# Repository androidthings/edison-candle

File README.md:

Edison Candle
=============
The Edison Candle is an example of building a production device using a
System-on-Module (SoM) running Android Things.
This repository contains the application software.
You can find the hardware schematic, layout, and bill of materials (BOM) hosted
on [CircuitHub](https://circuithub.com/projects/androidthings/edison-candle).

Prerequisites
-------------

- Carrier board from
  [CircuitHub](https://circuithub.com/projects/androidthings/edison-candle)
- Edison compute module ([SparkFun](https://www.sparkfun.com/products/13024))
- Edison mounting hardware ([SparkFun](https://www.sparkfun.com/products/13187))
- Orange LED ([SparkFun](https://www.sparkfun.com/products/12645))
- Yellow LED ([SparkFun](https://www.sparkfun.com/products/10634))
- Android Studio 2.2+

Getting Started
----------------

1.  Assemble the hardware components
2.  Import the project into Android Studio
3.  Connect the Edison to USB
4.  In Android Studio, click on the "Run" button.

If you prefer to run on the command line, type
```bash
./gradlew installDebug
adb shell am start com.example.androidthings.candle/.HomeActivity
```

Prototype Schematic
--------------------

You may also choose to run the sample on an Edison developer kit, with the
necessary peripherals connected as shown below:

Enable auto-launch behavior
---------------------------

This sample app is currently configured to launch only when deployed from your
development machine. To enable the main activity to launch automatically on boot,
add the following `intent-filter` to the app's manifest file:

```xml
<activity ...>

    <intent-filter>
        <action android:name="android.intent.action.MAIN"/>
        <category android:name="android.intent.category.HOME"/>
        <category android:name="android.intent.category.DEFAULT"/>
    </intent-filter>

</activity>
```

License
-------

Copyright 2017 The Android Open Source Project, Inc.

Licensed to the Apache Software Foundation (ASF) under one or more contributor
license agreements.  See the NOTICE file distributed with this work for
additional information regarding copyright ownership.  The ASF licenses this
file to you under the Apache License, Version 2.0 (the "License"); you may not
use this file except in compliance with the License.  You may obtain a copy of
the License at

  http://www.apache.org/licenses/LICENSE-2.0

Unless required by applicable law or agreed to in writing, software
distributed under the License is distributed on an "AS IS" BASIS, WITHOUT
WARRANTIES OR CONDITIONS OF ANY KIND, either express or implied.  See the
License for the specific language governing permissions and limitations under
the License.

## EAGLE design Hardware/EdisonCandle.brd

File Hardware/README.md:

Edison Candle Hardware
======================

This directory contains the hardware design files for the Edison Candle
production carrier board. The current revision was built using EAGLE.

Libraries
---------

The following EAGLE libraries were used in this design:

-   [SparkFun Blocks Template](https://github.com/sparkfun/Sparkfun_Blocks_Template)
    -   Provides Edison compute module and PCB footprint.
-   [SparkFun Eagle Libraries](https://github.com/sparkfun/SparkFun-Eagle-Libraries)
    -   Provides common components, such as the USB Micro connector.

License
-------

The hardware design files are released under the
[Creative Commons 4.0 International](http://creativecommons.org/licenses/by/4.0/)
license.

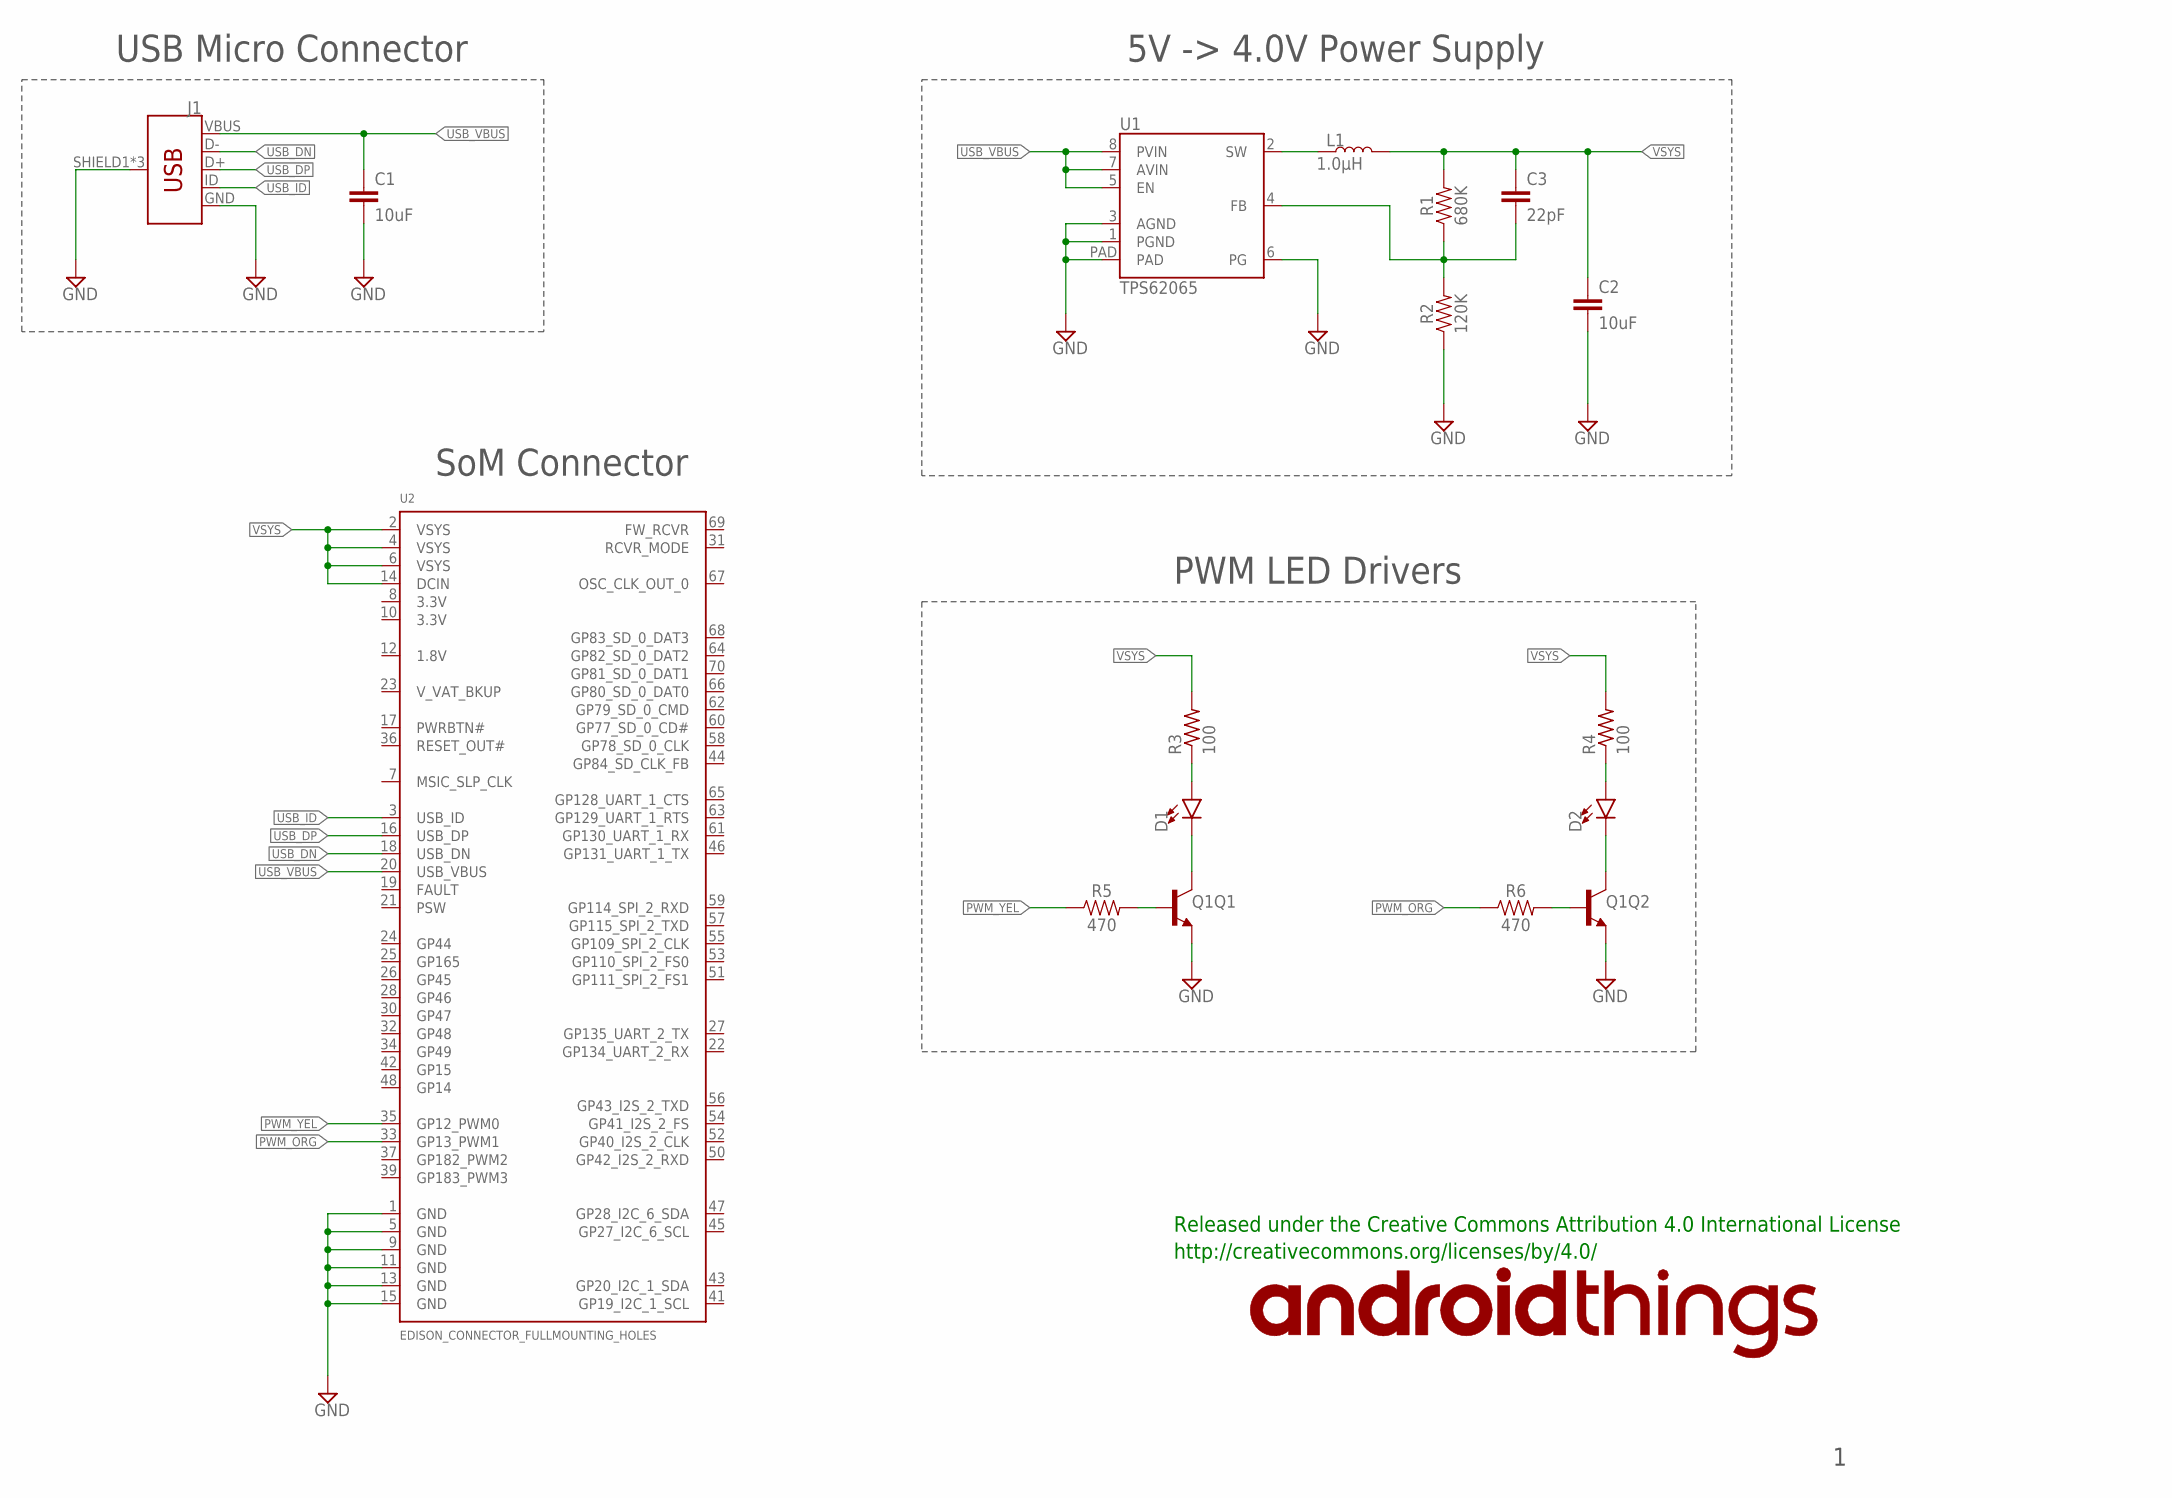
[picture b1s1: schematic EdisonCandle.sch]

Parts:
C1, C2: 10uF; 0805; MPN GRM21BR71A106KE51K
C3: 22pF; 0603; MPN 06035C220JAT2A
D1, D2: LED10MM; LED_10MM
J1: USB_MICRO-B_FEMALE-SMT; USB-B-MICRO-SMD; MPN 10104110-0001LF
L1: 1.0µH; SRP4020; MPN SRP4020-1R0M
Q1: TRANS_NPN_DUAL-MBT3904DW1T1; SC70-6; MPN MBT3904DW1T1G
R1: 680K; 0603; MPN ERJ-3EKF6803V
R2: 120K; 0603; MPN ERJ-3EKF1203V
R3, R4: 100; M1206; MPN RC1206FR-07100RL
R5, R6: 470; 0603; MPN ERJ-3EKF4700V
U1: TPS62065; WSON-8-PAD; MPN TPS62065DSGR
U2: EDISON_CONNECTOR_FULLMOUNTING_HOLES; EDISON_DAUGHTER; MPN DF40HC(3.0)-70DS-0.4V(58)

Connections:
GND: C1.2, C2.2, J1.GND, J1.SHIELD1 (SHIELD), J1.SHIELD2 (SHIELD), J1.SHIELD3 (SHIELD), Q1.1 (E), Q1.4 (E), R2.1, U1.1 (PGND), U1.3 (AGND), U1.6 (PG), U1.PAD, U2.1 (GND), U2.5 (GND), U2.9 (GND), U2.11 (GND), U2.13 (GND), U2.15 (GND)
unnamed: L1.1, U1.2 (SW)
unnamed: D1.A, R3.1
unnamed: C3.2, R1.1, R2.2, U1.4 (FB)
unnamed: D2.A, R4.1
unnamed: D1.C, Q1.3 (C)
unnamed: D2.C, Q1.6 (C)
unnamed: Q1.5 (B), R5.2
unnamed: Q1.2 (B), R6.2
PWM_ORG: R6.1, U2.33 (GP13_PWM1)
PWM_YEL: R5.1, U2.35 (GP12_PWM0)
USB_DN: J1.D-, U2.18 (USB_DN)
USB_DP: J1.D+, U2.16 (USB_DP)
USB_ID: J1.ID, U2.3 (USB_ID)
USB_VBUS: C1.1, J1.VBUS, U1.5 (EN), U1.7 (AVIN), U1.8 (PVIN), U2.20 (USB_VBUS)
VSYS: C2.1, C3.1, L1.2, R1.2, R3.2, R4.2, U2.2 (VSYS), U2.4 (VSYS), U2.6 (VSYS), U2.14 (DCIN)

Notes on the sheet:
SoM Connector
PWM LED Drivers
USB Micro Connector
5V -> 4.0V Power Supply
Released under the Creative Commons Attribution 4.0 International License
http://creativecommons.org/licenses/by/4.0/

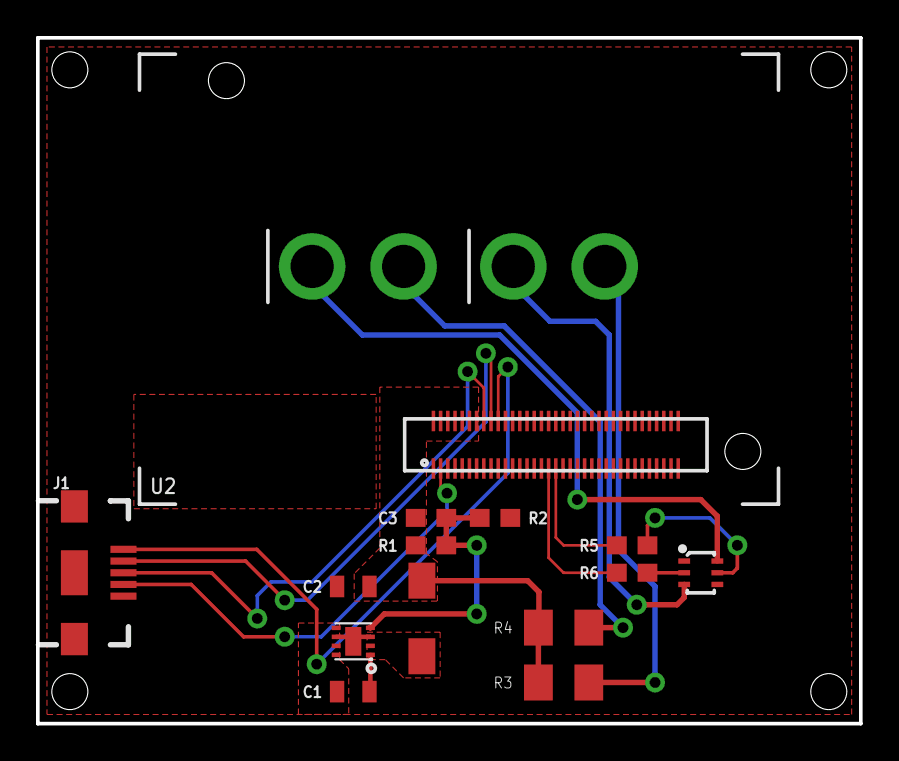
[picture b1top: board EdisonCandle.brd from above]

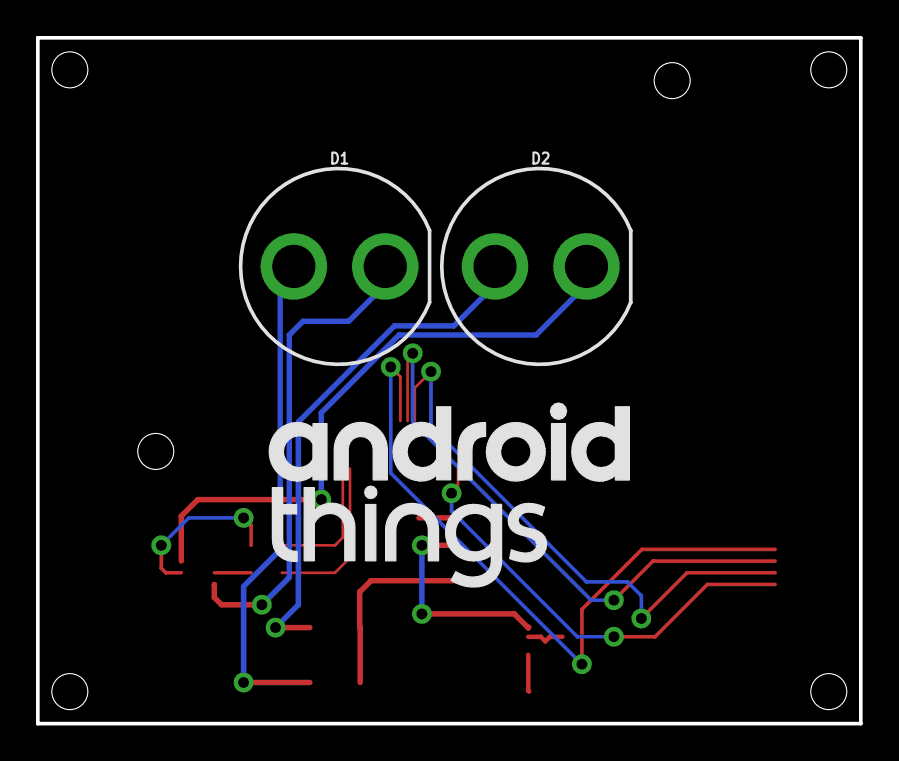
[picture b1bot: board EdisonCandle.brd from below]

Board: 2 copper layers, 45.7 x 38.1 mm, 17 parts (3 on the bottom side), 16 nets.

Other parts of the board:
U$2: ATHINGS_LOGO_STACKED_20MM

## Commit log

2017-05-09 Initial production candle sample.
2017-05-09 Add Hardware License
2017-05-09 Include readable hardware schematic version.
2017-05-11 Hardware README cleanup.
2017-10-10 Move prototype schematics.
2017-10-10 Remove nested app directory.
2018-03-01 Update to android things sdk 0.7 and new drivers
    Updated to use Android Things SDK 0.7-devpreview
    Updated to the API changes in DP7
    Bug: 71717279
2018-04-05 Make launch behavior optional.
    Bug: 72950561
2018-04-06 Update to android things sdk 0.8 and API 27
    Updated to use Android Things SDK 0.8-devpreview
    Updated to the API changes in DP8
    Updated to use Android API 27
    Removed buildToolsVersion
    Add nocompress to *.so files on tensorflow imageclassifier
    Bug: 72671975
2018-04-10 edison-candle: clean up manifest
    - remove icon, backup and rtl attributes
    - remove extra spaces
    - add PIO permission
    Bug: 77575481
    Bug: 77478121
2018-05-05 Update to android things sdk 1.0
    Updated to use Android Things SDK 1.0
    Bug: 79286237

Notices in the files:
parts and their libraries:
SparkFun-Capacitors: Licensing: Creative Commons ShareAlike 4.0 International - https://creativecommons.org/licenses/by-sa/4.0
